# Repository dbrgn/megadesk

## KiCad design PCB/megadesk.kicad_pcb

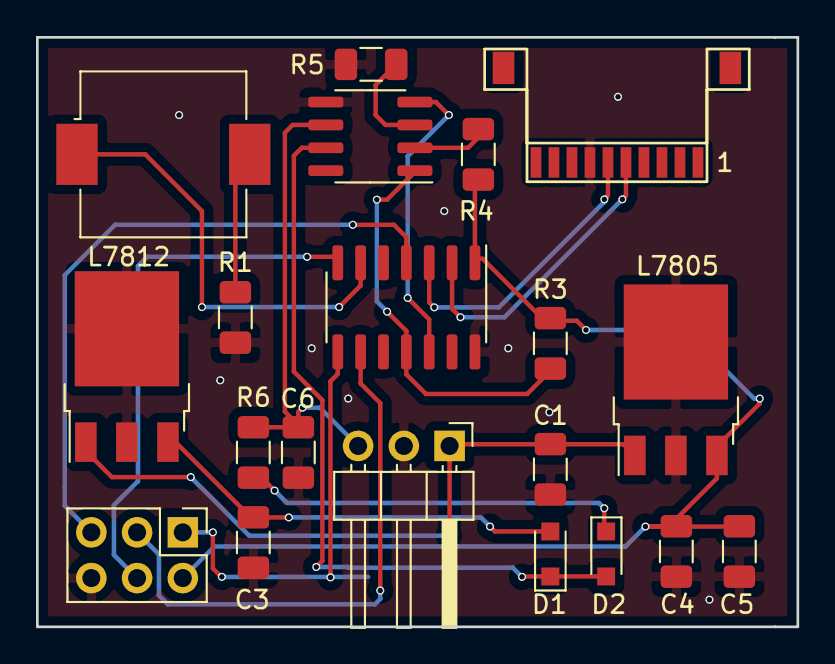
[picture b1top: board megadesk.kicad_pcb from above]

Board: 2 copper layers, 42.2 x 32.8 mm, 20 parts (0 on the bottom side), 19 nets.

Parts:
BZ1: Buzzer; Buzzer_Murata_PKMCS0909E4000-R1-HAND-SOLDER
C1: 0.33uF; C_1206_3216Metric
C3, C4, C5: 0.1uF; C_1206_3216Metric
C6: 220pF; C_1206_3216Metric
D1, D2: 1N4148; D_SOD-323_HandSoldering
J1: Interface; Pin_Header_Angled_1x03_Pitch2.54mm
J2: FFC; FFC_10
J3: AVR-ISP-6; PinHeader_2x03_P2.54mm_Vertical
R1, R6: 1k; R_1206_3216Metric
R3, R4, R5: 4.7k; R_1206_3216Metric
U1: L7812; TO-252-3_TabPin2
U2: L7805; TO-252-3_TabPin2
U3: ATTINY841-SSU; SOIC-14_3.9x8.7mm_P1.27mm
U4: MCP2003B; SOIC-8_3.9x4.9mm_P1.27mm

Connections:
+5V: C4.1, C5.1, J3.2, R3.1, R4.2, U2.3, U3.1
+12V: C3.1, D1.2, U1.3
+24V: C1.1, J1.1, U1.1, U2.1
Bdown: J2.6, U3.3
Bup: J2.5, U3.2
GND: C1.2, C3.2, C4.2, C5.2, C6.2, J1.2, J2.7, J3.6, R1.2, R5.2, U1.2, U2.2, U3.14, U4.5
LINBUS: C6.1, J1.3, R6.2, U4.6
MISO: J3.1, U3.8
MOSI: J3.4, U3.7
unnamed: BZ1.1, U3.6
unnamed: BZ1.2, R1.1
unnamed: D1.1, D2.2, U4.7
unnamed: D2.1, R6.1
unnamed: R3.2, U3.11, U4.1
unnamed: R4.1, U4.2
unnamed: R5.1, U4.3
unnamed: U3.12, U4.4
RST: J3.5, U3.4
SCK: J3.3, U3.9

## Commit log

2021-01-29 Coredump adjustments
